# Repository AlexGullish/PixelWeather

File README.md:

# PixelWeather

**A compact ESP32-powered weather station with a colour TFT display and live weather data from Open-Meteo.**

PixelWeather is an embedded weather dashboard built on an ESP32  board and a TFT display. It retrieves live weather information from the Open-Meteo API, and displays current conditions and daily forecasts

## Features

- **Live weather data:** Retrieves current weather conditions using the Open-Meteo Forecast API.
- **Three display screens:** Switch between current weather, atmospheric conditions, and daily forecasts.
- **Automatic updates:** Refreshes weather data every 15 minutes.
- **Manual refresh:** Update weather information by pressing the refresh button

## Display Interface

The interface  contains three screens:

**01 — Current Weather**
- Current temperature
- Feels-like temperature
- Weather description

**02 — Conditions**
- Relative humidity
- Wind speed

**03 — Daily Forecast**
- Daily maximum temperature
- Daily minimum temperature

### Button Controls

| Button | Function |
|---|---|
| Refresh | Manually retrieve updated weather data |
| Next Screen | Cycle through the three display screens |

Weather data is automatically refreshed every 15 minutes. Failed updates trigger a shorter retry interval.

## BOM
| Item             | Qty | Supplier  | Cost/item | Total Cost | link                                                                                     |
|------------------|-----|-----------|-----------|------------|------------------------------------------------------------------------------------------|
| LCD Display      | 1   | Waveshare | $8.99     | $8.99      | https://www.waveshare.com/1.8inch-lcd-module.htm                                         |
| PCB              | 1   | JLCPCB    | $7.20     | $7.20      | https://cart.jlcpcb.com/quote?rand=0.7472206825568115                                    |
| 1x9 Dupont Case  | 2   | BerryBase | $0.07     | $0.14      | https://www.berrybase.ch/dupont-gehaeuse-1x9-pin                                         |
| 1x10 Dupont Case | 2   | BerryBase | $0.10     | $0.20      | https://www.berrybase.ch/dupont-gehaeuse-1x10-pin                                        |
| Pin Strip        | 1   | BerryBase | $0.25     | $0.25      | https://www.berrybase.ch/stiftleiste-1x-20-polig-rm-2-54-gerade                          |
| Push Button      | 2   | BerryBase | $0.25     | $0.50      | https://www.berrybase.ch/en/short-stroke-pushbutton-vertical-pcb-mounting-6x6mm-h-13.0mm |
| Estimated total  | 1   |           |           | $17.28      |                                                                                          |

The ESP is already owned and therefore funding for it is not required

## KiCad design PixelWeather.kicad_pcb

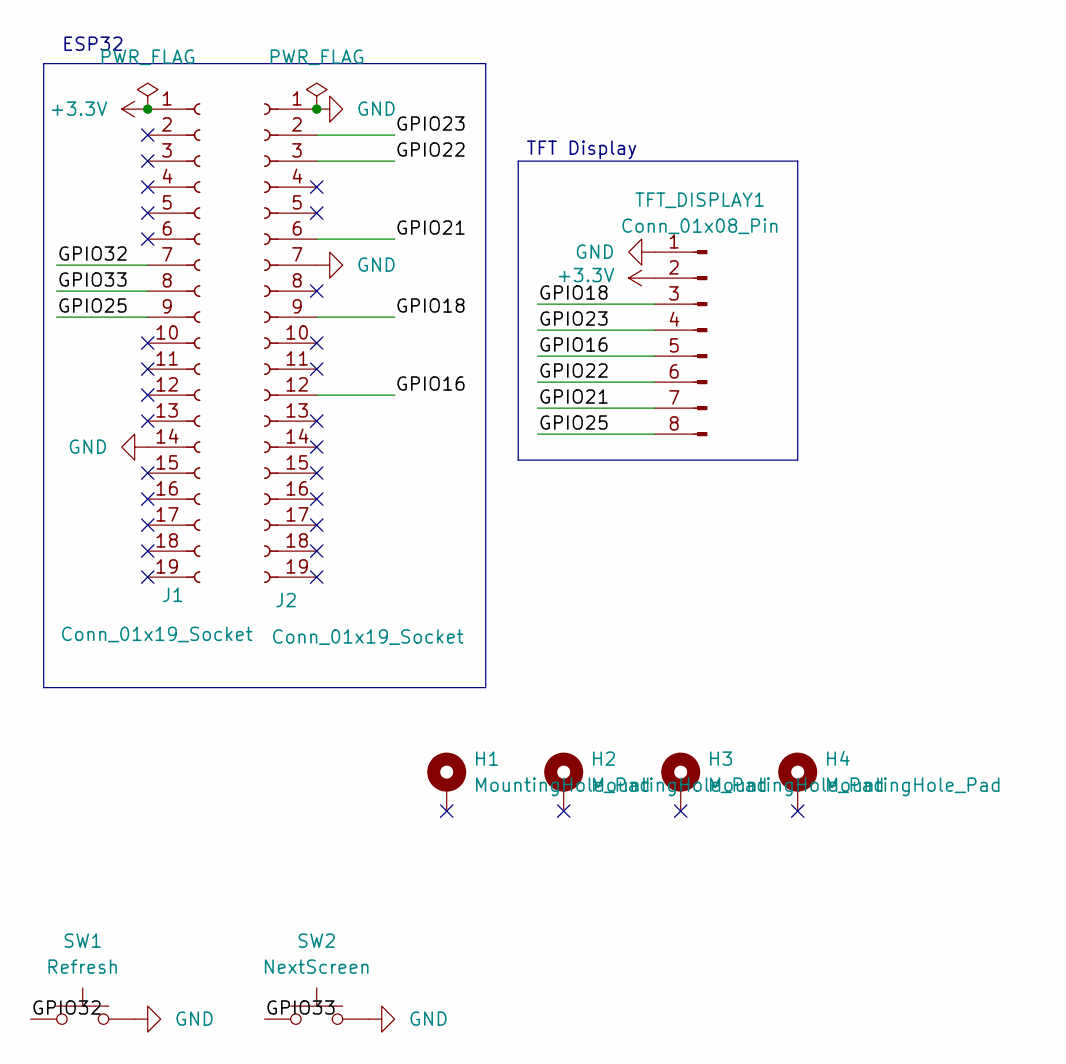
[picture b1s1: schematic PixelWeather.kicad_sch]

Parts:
H1, H2, H3, H4: MountingHole_Pad; MountingHole_2.2mm_M2
J1, J2: Conn_01x19_Socket; PinSocket_1x19_P2.54mm_Vertical
SW1: Refresh; SW_PUSH_6mm
SW2: NextScreen; SW_PUSH_6mm
TFT_DISPLAY1: Conn_01x08_Pin; PinHeader_1x08_P2.00mm_Vertical

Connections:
+3.3V: J1.1, TFT_DISPLAY1.2
/GPIO16: J2.12, TFT_DISPLAY1.5
/GPIO18: J2.9, TFT_DISPLAY1.3
/GPIO21: J2.6, TFT_DISPLAY1.7
/GPIO22: J2.3, TFT_DISPLAY1.6
/GPIO23: J2.2, TFT_DISPLAY1.4
/GPIO25: J1.9, TFT_DISPLAY1.8
/GPIO32: J1.7, SW1.1
/GPIO33: J1.8, SW2.1
GND: J1.14, J2.1, J2.7, SW1.2, SW2.2, TFT_DISPLAY1.1

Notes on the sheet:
ESP32
TFT Display

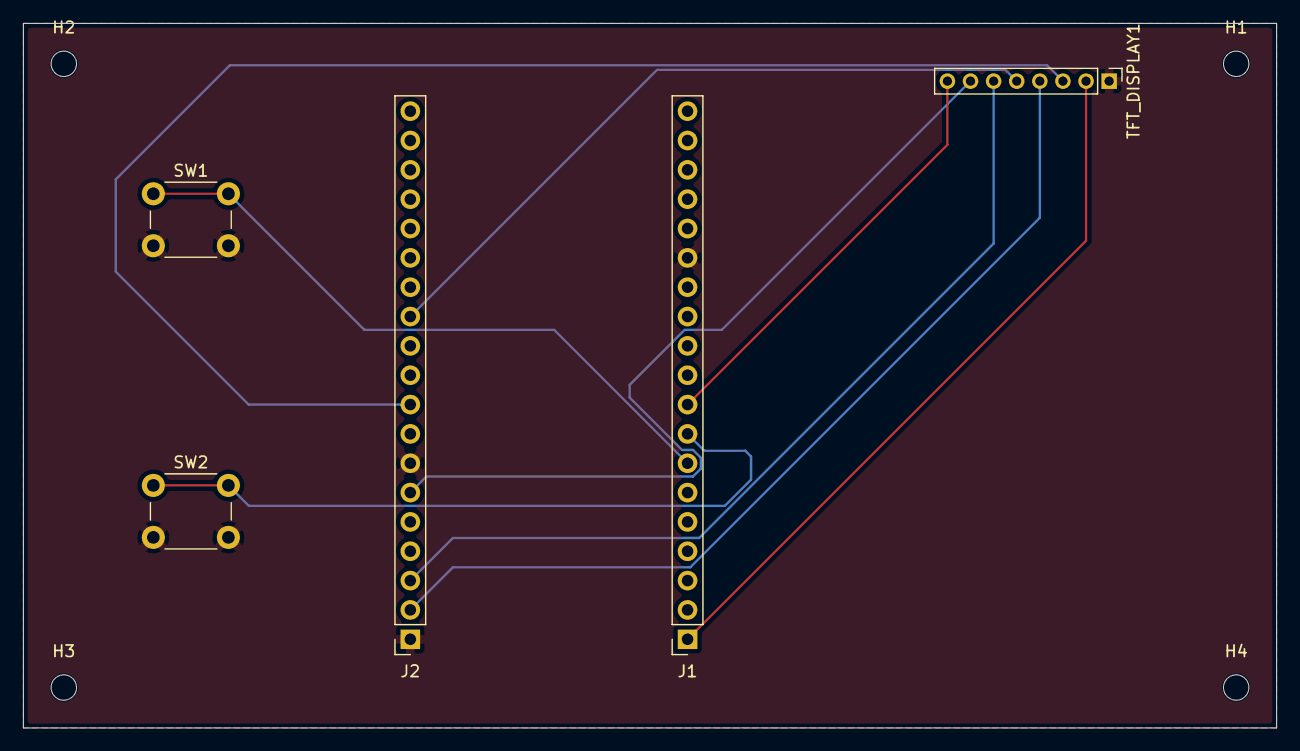
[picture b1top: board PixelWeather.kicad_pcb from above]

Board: 2 copper layers, 108.5 x 61.0 mm, 9 parts (0 on the bottom side), 10 nets.
